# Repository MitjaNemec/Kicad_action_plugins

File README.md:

## NOTICE ##

These plugins work only on old KiCad version (5.1.x).

The plugins that work under newer versions (V5, V6, ...) should be available under the KiCad's built in Plugin and Content Manager (PCM).

Currently (2023) there are four plugins available:
- Replicate Layout plugin (https://github.com/MitjaNemec/ReplicateLayout)
- Place Footprints plugin (https://github.com/MitjaNemec/PlaceFootprints)
- Save/Restore layout plugin (https://github.com/MitjaNemec/SaveRestoreLayout)
- Archive 3D models plugin (https://github.com/MitjaNemec/Archive3DModels)

# KiCad Action Plugins

This repository contains KiCad pcbnew Action Plugins.

__All plugins have been tested on Kicad 5.1.x__ on Windows 7 / Windows 10. You need to have `KICAD_SCRIPTING_WXPYTHON` enabled. They should also work on GNU/Linux distributions and MacOS, even with Python3.

**KiCad V6 info**

Plugins for KiCad V6 will be avialible in KiCads __Plugin and Content Manager__ as they are ported. Some of them will not be ported.

## Installation

The following instructions are for KiCad 5.1.x

### Windows 7/Windows 10

Install the plugins in:
    `%APPDATA%\scripting\plugins` (which most commonly translates to `C:\Users\username\AppData\Roaming\kicad\scripting\plugins`)

### GNU/Linux

Install the plugins in:
    `~/.kicad/scripting/plugins` or
    `~/.kicad_plugins`

If you have no other action plugins, you can use this script:

```
 SPDIR=~/.kicad_plugins
 mkdir -pv `dirname ${SPDIR}` 2>/dev/null
 cd `dirname ${SPDIR}` && git clone --depth 1 git@github.com:MitjaNemec/Kicad_action_plugins.git && \
  ln -s Kicad_action_plugins `basename ${SPDIR}` && cd ${SPDIR} && echo && \
  echo "Installed action plugins:" && find . -d 1 -type d |grep -v '.git' |sed 's/^\.\// * /'
```

To update your action plugins from this repository in future:

```
 SPDIR=~/.kicad_plugins
 cd ${SPDIR} && git pull
```

### Mac

Install the plugins in:
    `~/Library/Application Support/kicad/scripting/plugins` or on newer versions (eg. 5.1.10)
    `~/Library/Preferences/kicad/scripting/plugins`

If you have no other action plugins, you can use this script:

```
 SPDIR=~/Library/Preferences/kicad/scripting/plugins
 mkdir -pv `dirname ${SPDIR}` 2>/dev/null
 cd `dirname ${SPDIR}` && git clone --depth 1 git@github.com:MitjaNemec/Kicad_action_plugins.git && \
  ln -s Kicad_action_plugins `basename ${SPDIR}` && cd ${SPDIR} && echo && \
  echo "Installed action plugins:" && find . -d 1 -type d |grep -v '.git' |sed 's/^\.\// * /'
```

To update your action plugins from this repository in future:

```
 SPDIR=~/Library/Preferences/kicad/scripting/plugins
 cd ${SPDIR} && git pull
```

## Plugins
 
### Replicate layout

The purpose of this plugin is to replicate layout sections. The replication is based upon hierarchical sheets in eeschema.
The basic requirement for replication is that the section to be replicated (source) is completely contained within a single hierarchical sheet, and replicated sections (destination) are just copies of the same sheet. Complex hierarchies are supported therefore replicated sheet can contain subsheets. The plugin replicates footprints, zones, tracks, text adn drawings.

After the section for replication (source section) has been laid out (footprints, tracks, text objects and zones placed) you need to:
1. Place the anchor footprints for the destiantion sections you want to replicate. This defines the position and orientation of replicated sections. You can use [Place footprints] action plugin for this.
2. Select the same anchor footprint within the source section.
3. Run the plugin.
4. Choose which hierarchical level you wish to replicate.
5. Select which sheets you want to replicate (default is all of them)
6. Select whether you want to replicate also tracks, zones and/or text objects.
7. Select whether you want to replicate tracks/zones/text which intersect the pivot bounding box or just those contained within the bounding box.
8. Select whether you want to delete already laid out tracks/zones/text (this is useful when updating an already replicated layout).
9. Hit OK.

By default, only objects which are fully contained in the bounding box constituted by all the footprints in the section will be replicated. You can select to also replicate zones and tracks which intersect this bounding box. Additionally, tracks, text and zones which are already laid out in the replicated bounding boxes can be removed (useful when updating). Note that bounding boxes are squares aligned with the x and y axis, regardless of section orientation.

Example replication of a complex hierarchical project. Replicating inner sheet first, then outer.

### Place footprints

This plugin will place footprints in:
- in line
- circular
- in square matrix

The plugins for placement are selected either by consecutive reference numbers or by same ID on different hierarchical sheets.

If you want to place the footprints by consecutive reference numbers you have to
1. select a footprint which is first in the sequence to be placed
2. run the plugin
3. select which place by reference number
4. choose which footprint in the sequence you want to place
5. select the arrangement (linear, matrix, circular)
6. select place dimension (step in x and y axes in linear and matrix mode and angle step and radius in circular mode)
7. run the plugin

If you want to place the footprints by same ID with
1. select a footprint which is first in the sequence to be placed
2. run the plugin
3. select the hierarchical level by which the footprints will be placed (in complex hierarchies)
4. choose from which sheets you want the footprint to place
5. select the arrangement (linear, matrix, circular)
6. select place dimension (step in x and y axes in linear and matrixc mode and angle step and radius in circlar mode)
7. run the plugin

Example of place by reference number

Example of place by sheet ID

### Delete Selected

This plugin deletes selected items. Items can be: zones and/or tracks and/or footprints. The main intention is to delete selected tracks in order to redo parts of the layout.

To run the plugin:
1. Select items you want to delete (note that in KiCad it is different if you start your selection box from left or right)
2. Run the plugin
3. Select what you want to delete
4. Hit OK

### pad2pad track distance

This plugin calculates the shortest distance between two pads. Use with caution because the result is not always correct as the algorithm follows the track layout. Also, the Via distance is not accounted for. The following picture shows an example where the distance is not correct. Here, the algorithm calculates the distance from the first pad to pin #4 and then to the other pad. It does not consider the connection between the two tracks at the encircled area where they actually branch off making the measured distance longer than it actually is.

For complex tracks (GND, Supply rails) the calculation can take quite some time.

To run the plugin:
1. Select two pads to measure the distance between
2. Run the plugin
3. Select what you want to delete
4. Hit OK

### net2net min distance

This plugin calculates the shortest distance between two tracks on different nets. To use, select one pad on first net and one pad on second net and run the plugin.

### Archive project

This plugin archives the project thus making it portable.

The schematics archive is achieved via the project cache library. The project cache library is copied to project-archive.lib which is modified and added to the project symbol library table (if the table does not exist it is created). Also the links to the symbols within the schematics are modified so that they point to the symbols within the archive library. Afterwards, the cache library is deleted. Eeschema will recreate a correct cache library the next time the schematics are edited.

The archiving of the pcb and its footprints is already implemented within pcbnew.

The 3D models archive is placed in "shapes3D" subfolder where all 3D models are copied.
Then, the links to the models within the layout (.kicad_pcb) file are modified so that they point to the archived 3D models with a path relative to the project folder.

The plugin is run from pcbnew. When the plugin is run, eeschema has to be closed. If the plugin finished successfully, it automatically closes pcbnew. This behaviour is expected and required to perform the operation.

If the project is modified later it should be archived again in order to stay portable. If a symbol of a unit has to be replaced, all units with the same symbol have to be deleted.

### Swap pins

This plugin swaps two pads (in layout) and their corresponding pins (in schematics). The pins in the schematics have to be connected to a local or global label or hierarchical label either directly or through a short wire segment. The plugin also works across multi-unit parts and/or across different hierarchical levels.

Only one pin can be connected. Currently "no connection" flags are not supported. Eeschema has to be closed when the plugin is executed in pcbnew. Once the plugin is done, you should save the layout. Note that using undo will only undo the change in the layout, but not the change in the schematics. To reverse the operation, you can run the plugin again.

Example of pin swapping

### Swap units

This plugin swaps two units (in layout) and r units (in schematics). Eeschema has to be closed when the plugin is executed in pcbnew. Unit swapping work across hierarchical pages.  Note that using undo will only undo the change in the layout, but not the change in the schematics. To reverse the operation, you can run the plugin again.

Example of unit swapping

### Length stats

This plugin displays length of all tracks on selected nets. This can be used for length matching.

Workflow:
1. Select tracks or pads on nets you want the length displayed. You can also select a footprint(s)
2. Run the plugin. You can remove redundant nets
3. Lay the tracks
4. Close the track length window

Example:

### Save/Restore Layout

This plugin saves the partial layout of a selected pcb (only specific hierarchical level is saved). This layout can be imported into another pcb, if it is based upon the same hierarchical subsheets. The equality is tested and checked.

Workflow:
1. Select one footprint which is in the hierarchy that you want to save the layout for.
2. Run the plugin and choose "Save layout"
3. Select into which file should the layout be saved
4. Create a new project. Copy the chosen .sch files used for hierarchy to the project folder and link it into schematics
5. Create a new layout.
6. Place and select the anchor footprint. This defines the position and orientation of restored layout.
7. Run the plugin.
8. Choose "Restore layout"
9: Select in which file is tha layout data stored
10. Voila, observe restored layout

Example:

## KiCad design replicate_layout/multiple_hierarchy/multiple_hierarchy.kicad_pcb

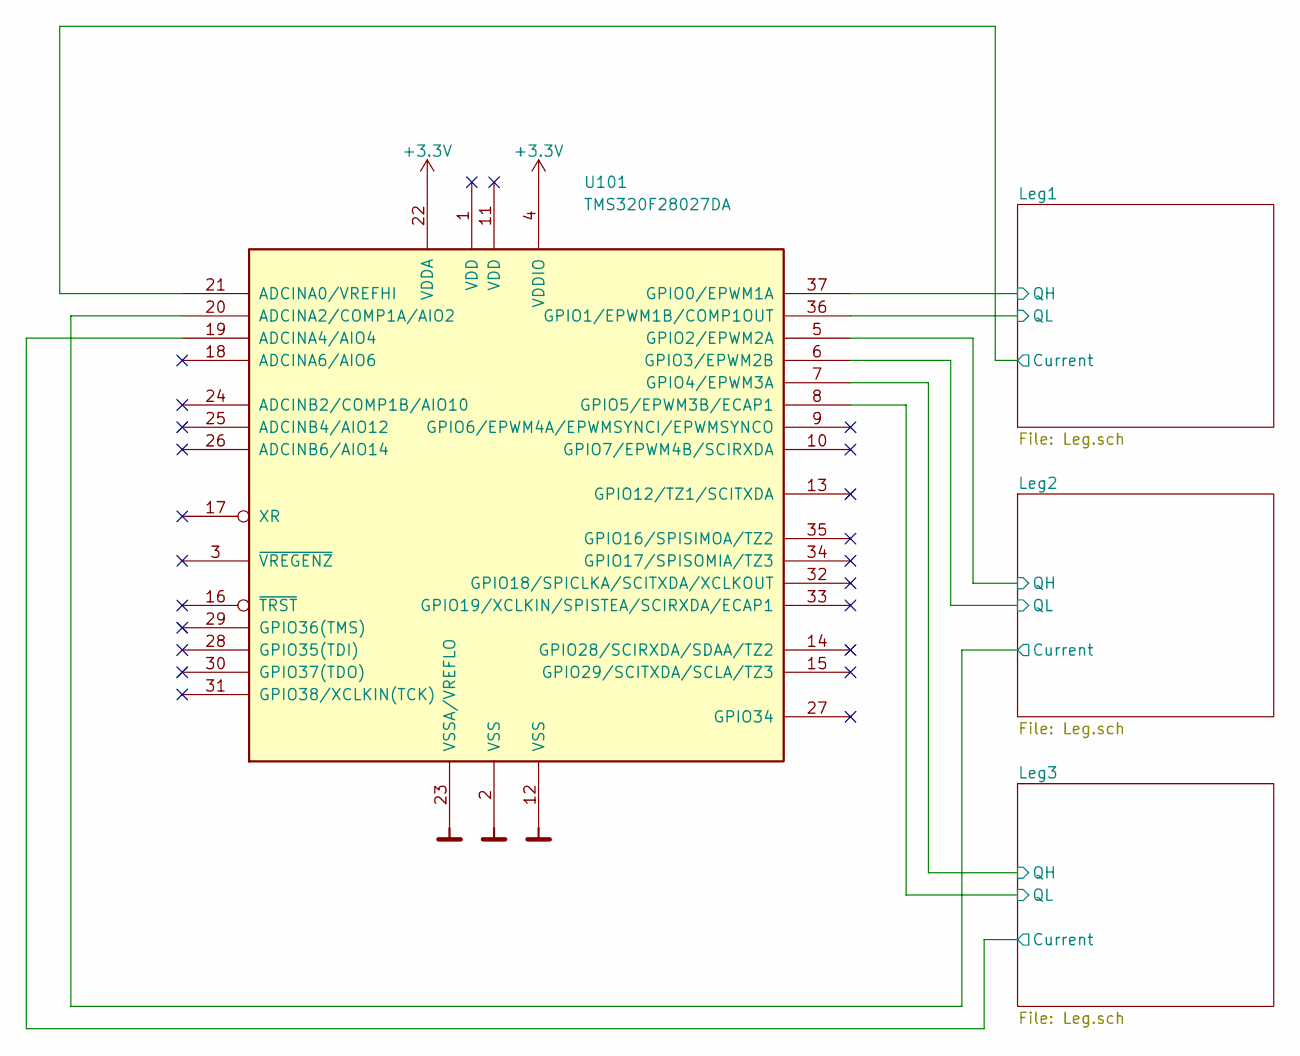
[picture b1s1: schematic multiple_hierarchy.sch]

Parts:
U101: TMS320F28027DA; TSSOP-38_4.4x9.7mm_P0.5mm

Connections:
+3V3: U101.4 (VDDIO), U101.22 (VDDA); also elsewhere on the board
-VDC: U101.2 (VSS), U101.12 (VSS), U101.23 (VSSA/VREFLO); also elsewhere on the board
/Leg1/Current: U101.21 (ADCINA0/VREFHI); also elsewhere on the board
/Leg1/QH: U101.37 (GPIO0/EPWM1A); also elsewhere on the board
/Leg1/QL: U101.36 (GPIO1/EPWM1B/COMP1OUT); also elsewhere on the board
/Leg2/Current: U101.20 (ADCINA2/COMP1A/AIO2); also elsewhere on the board
/Leg2/QH: U101.5 (GPIO2/EPWM2A); also elsewhere on the board
/Leg2/QL: U101.6 (GPIO3/EPWM2B); also elsewhere on the board
/Leg3/Current: U101.19 (ADCINA4/AIO4); also elsewhere on the board
/Leg3/QH: U101.7 (GPIO4/EPWM3A); also elsewhere on the board
/Leg3/QL: U101.8 (GPIO5/EPWM3B/ECAP1); also elsewhere on the board
/Power_extra/QH: U101.9 (GPIO6/EPWM4A/EPWMSYNCI/EPWMSYNCO); also elsewhere on the board
/Power_extra/Ql: U101.10 (GPIO7/EPWM4B/SCIRXDA); also elsewhere on the board

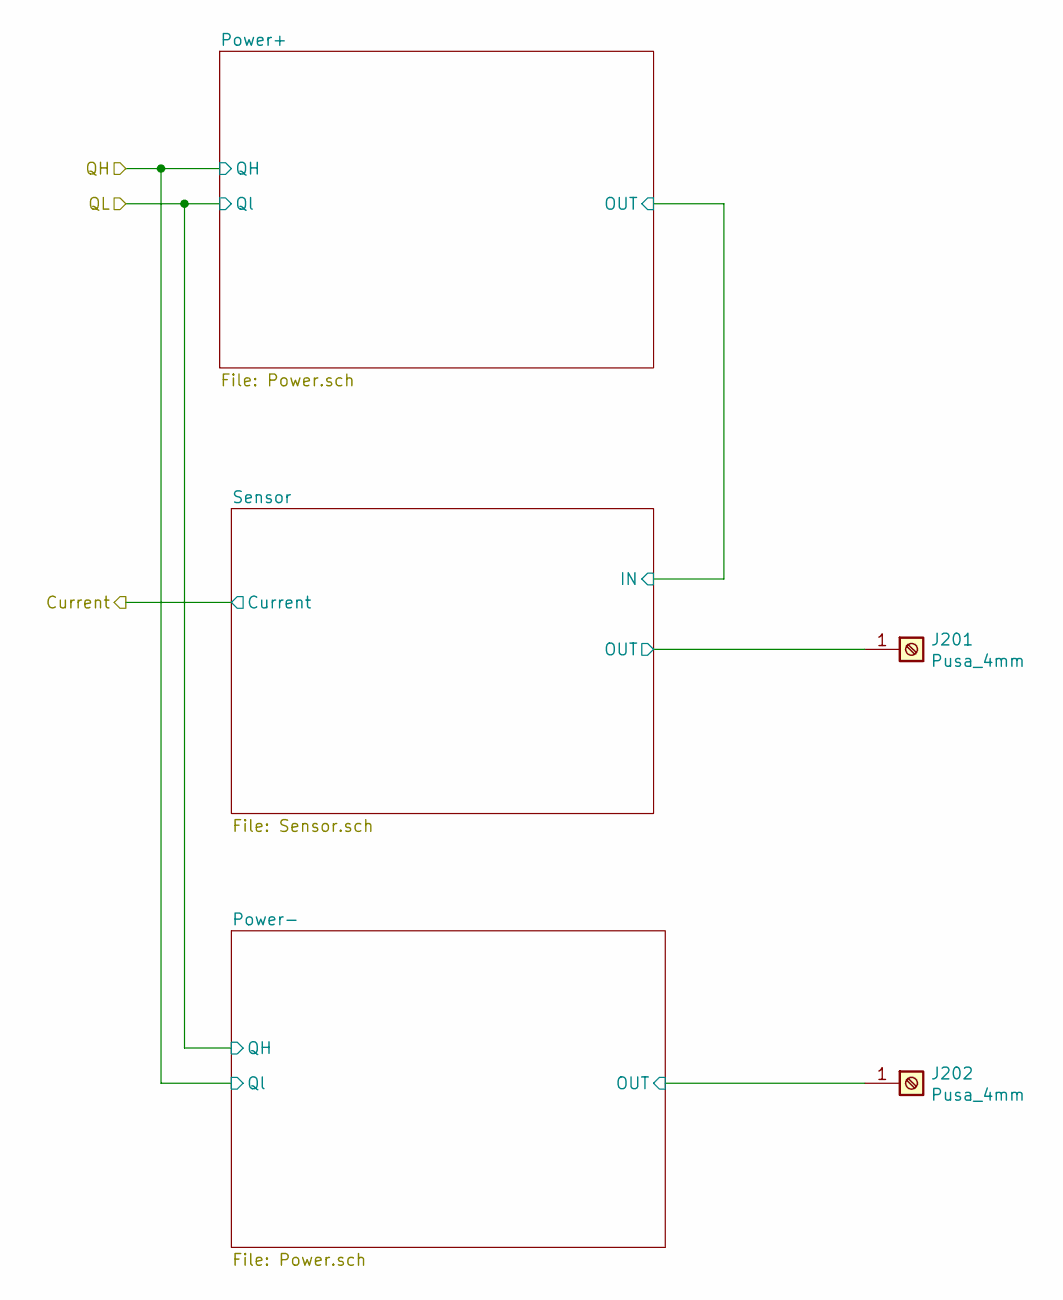
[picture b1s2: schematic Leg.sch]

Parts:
J201, J202: Pusa_4mm

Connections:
/Leg1/Power-/OUT: J202.1; also elsewhere on the board
/Leg1/Sensor/OUT: J201.1; also elsewhere on the board

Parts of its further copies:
J601, J602, J1001, J1002: Pusa_4mm

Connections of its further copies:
/Leg2/Power-/OUT: J602.1; also elsewhere on the board
/Leg2/Sensor/OUT: J601.1; also elsewhere on the board
/Leg3/Power-/OUT: J1002.1; also elsewhere on the board
/Leg3/Sensor/OUT: J1001.1; also elsewhere on the board

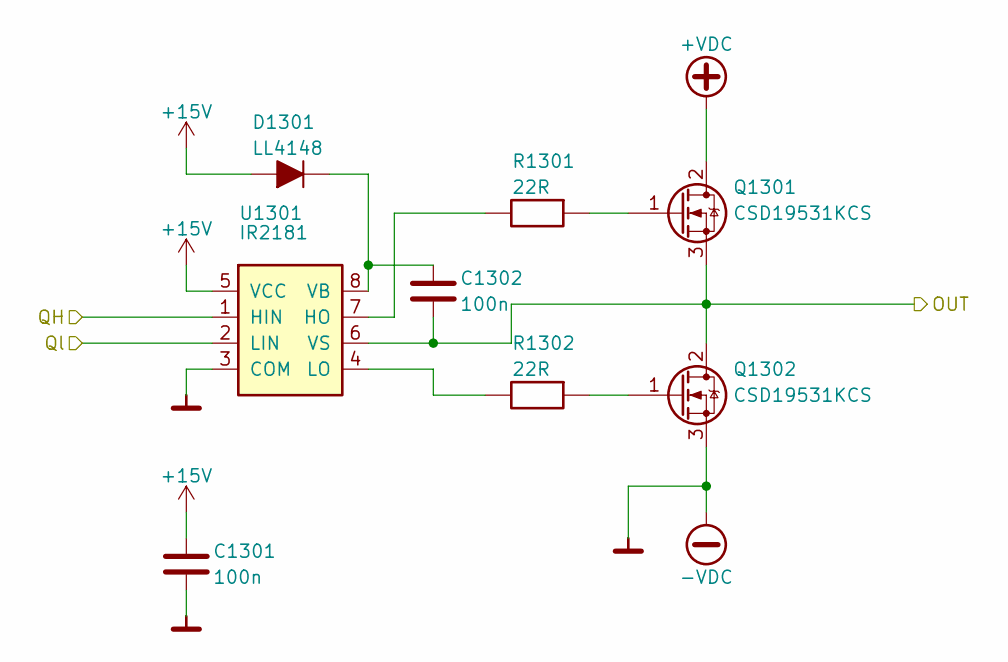
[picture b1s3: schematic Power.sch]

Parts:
C301, C302: 100n; C1206M
D301: LL4148; D_MiniMELF
Q301, Q302: CSD19531KCS; TO-220
R301, R302: 22R; R1206M
U301: IR2181; SO8

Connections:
+15V: C301.1, D301.2 (A), U301.5 (VCC); also elsewhere on the board
+VDC: Q301.2 (D); also elsewhere on the board
-VDC: C301.2, Q302.3 (S), U301.3 (COM); also elsewhere on the board
/Leg1/QH: U301.1 (HIN); also elsewhere on the board
/Leg1/QL: U301.2 (LIN); also elsewhere on the board
/Leg1/Sensor/IN: C302.2, Q301.3 (S), Q302.2 (D), U301.6 (VS); also elsewhere on the board
unnamed: C302.1, D301.1 (K), U301.8 (VB)
unnamed: Q301.1 (G), R301.2
unnamed: Q302.1 (G), R302.2
unnamed: R301.1, U301.7 (HO)
unnamed: R302.1, U301.4 (LO)

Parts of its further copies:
C501, C502, C701, C702, C901, C902, C1101, C1102, C1301, C1302: 100n; C1206M
D501, D701, D901, D1101, D1301: LL4148; D_MiniMELF
Q501, Q502, Q701, Q702, Q901, Q902, Q1101, Q1102, Q1301, Q1302: CSD19531KCS; TO-220
R501, R502, R701, R702, R901, R902, R1101, R1102, R1301, R1302: 22R; R1206M
U501, U701, U901, U1101, U1301: IR2181; SO8

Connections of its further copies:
+15V: C501.1, C701.1, C901.1, C1101.1, C1301.1, D501.2 (A), D701.2 (A), D901.2 (A), D1101.2 (A), D1301.2 (A), U501.5 (VCC), U701.5 (VCC), U901.5 (VCC), U1101.5 (VCC), U1301.5 (VCC); also elsewhere on the board
+VDC: Q501.2 (D), Q701.2 (D), Q901.2 (D), Q1101.2 (D), Q1301.2 (D); also elsewhere on the board
-VDC: C501.2, C701.2, C901.2, C1101.2, C1301.2, Q502.3 (S), Q702.3 (S), Q902.3 (S), Q1102.3 (S), Q1302.3 (S), U501.3 (COM), U701.3 (COM), U901.3 (COM), U1101.3 (COM), U1301.3 (COM); also elsewhere on the board
/Leg1/Power-/OUT: C502.2, Q501.3 (S), Q502.2 (D), U501.6 (VS); also elsewhere on the board
/Leg1/QH: U501.2 (LIN); also elsewhere on the board
/Leg1/QL: U501.1 (HIN); also elsewhere on the board
/Leg2/Power-/OUT: C902.2, Q901.3 (S), Q902.2 (D), U901.6 (VS); also elsewhere on the board
/Leg2/QH: U701.1 (HIN), U901.2 (LIN); also elsewhere on the board
/Leg2/QL: U701.2 (LIN), U901.1 (HIN); also elsewhere on the board
/Leg2/Sensor/IN: C702.2, Q701.3 (S), Q702.2 (D), U701.6 (VS); also elsewhere on the board
/Leg3/Power-/OUT: C1302.2, Q1301.3 (S), Q1302.2 (D), U1301.6 (VS); also elsewhere on the board
/Leg3/QH: U1101.1 (HIN), U1301.2 (LIN); also elsewhere on the board
/Leg3/QL: U1101.2 (LIN), U1301.1 (HIN); also elsewhere on the board
/Leg3/Sensor/IN: C1102.2, Q1101.3 (S), Q1102.2 (D), U1101.6 (VS); also elsewhere on the board
unnamed: C502.1, D501.1 (K), U501.8 (VB)
unnamed: C702.1, D701.1 (K), U701.8 (VB)
unnamed: C902.1, D901.1 (K), U901.8 (VB)
unnamed: C1102.1, D1101.1 (K), U1101.8 (VB)
unnamed: C1302.1, D1301.1 (K), U1301.8 (VB)
unnamed: Q501.1 (G), R501.2
unnamed: Q502.1 (G), R502.2
unnamed: Q701.1 (G), R701.2
unnamed: Q702.1 (G), R702.2
unnamed: Q901.1 (G), R901.2
unnamed: Q902.1 (G), R902.2
unnamed: Q1101.1 (G), R1101.2
unnamed: Q1102.1 (G), R1102.2
unnamed: Q1301.1 (G), R1301.2
unnamed: Q1302.1 (G), R1302.2
unnamed: R501.1, U501.7 (HO)
unnamed: R502.1, U501.4 (LO)
unnamed: R701.1, U701.7 (HO)
unnamed: R702.1, U701.4 (LO)
unnamed: R901.1, U901.7 (HO)
unnamed: R902.1, U901.4 (LO)
unnamed: R1101.1, U1101.7 (HO)
unnamed: R1102.1, U1101.4 (LO)
unnamed: R1301.1, U1301.7 (HO)
unnamed: R1302.1, U1301.4 (LO)

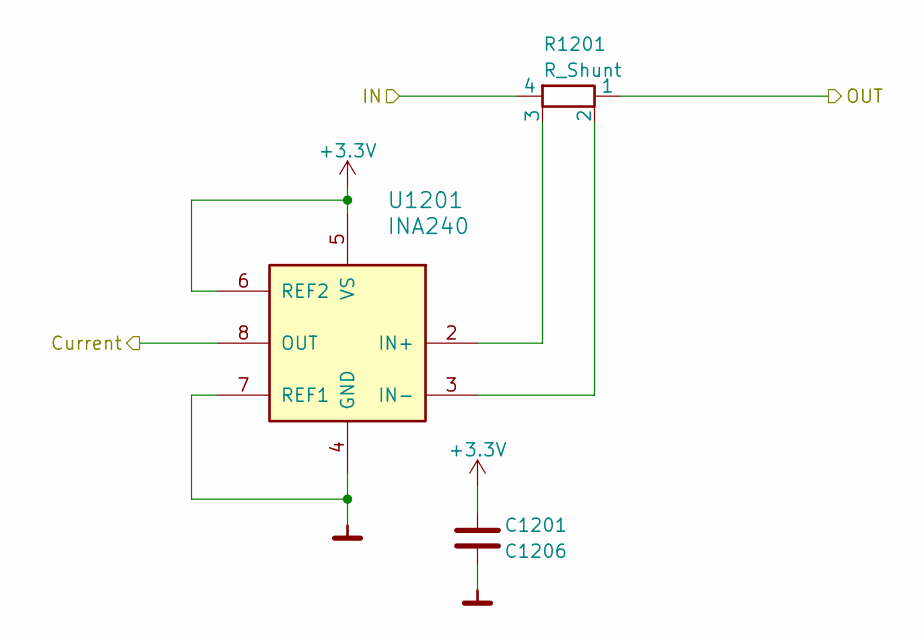
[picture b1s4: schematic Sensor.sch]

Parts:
C401: C1206; C1206M
R401: R_Shunt; RM
U401: INA240; TSSOP-8_4.4x3mm_P0.65mm

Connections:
+3V3: C401.1, U401.5 (VS), U401.6 (REF2); also elsewhere on the board
-VDC: C401.2, U401.4 (GND), U401.7 (REF1); also elsewhere on the board
/Leg1/Current: U401.8 (OUT); also elsewhere on the board
/Leg1/Sensor/IN: R401.4; also elsewhere on the board
/Leg1/Sensor/OUT: R401.1; also elsewhere on the board
unnamed: R401.2, U401.3 (IN-)
unnamed: R401.3, U401.2 (IN+)

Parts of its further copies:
C801, C1201: C1206; C1206M
R801, R1201: R_Shunt; RM
U801, U1201: INA240; TSSOP-8_4.4x3mm_P0.65mm

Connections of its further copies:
+3V3: C801.1, C1201.1, U801.5 (VS), U801.6 (REF2), U1201.5 (VS), U1201.6 (REF2); also elsewhere on the board
-VDC: C801.2, C1201.2, U801.4 (GND), U801.7 (REF1), U1201.4 (GND), U1201.7 (REF1); also elsewhere on the board
/Leg2/Current: U801.8 (OUT); also elsewhere on the board
/Leg2/Sensor/IN: R801.4; also elsewhere on the board
/Leg2/Sensor/OUT: R801.1; also elsewhere on the board
/Leg3/Current: U1201.8 (OUT); also elsewhere on the board
/Leg3/Sensor/IN: R1201.4; also elsewhere on the board
/Leg3/Sensor/OUT: R1201.1; also elsewhere on the board
unnamed: R801.2, U801.3 (IN-)
unnamed: R801.3, U801.2 (IN+)
unnamed: R1201.2, U1201.3 (IN-)
unnamed: R1201.3, U1201.2 (IN+)

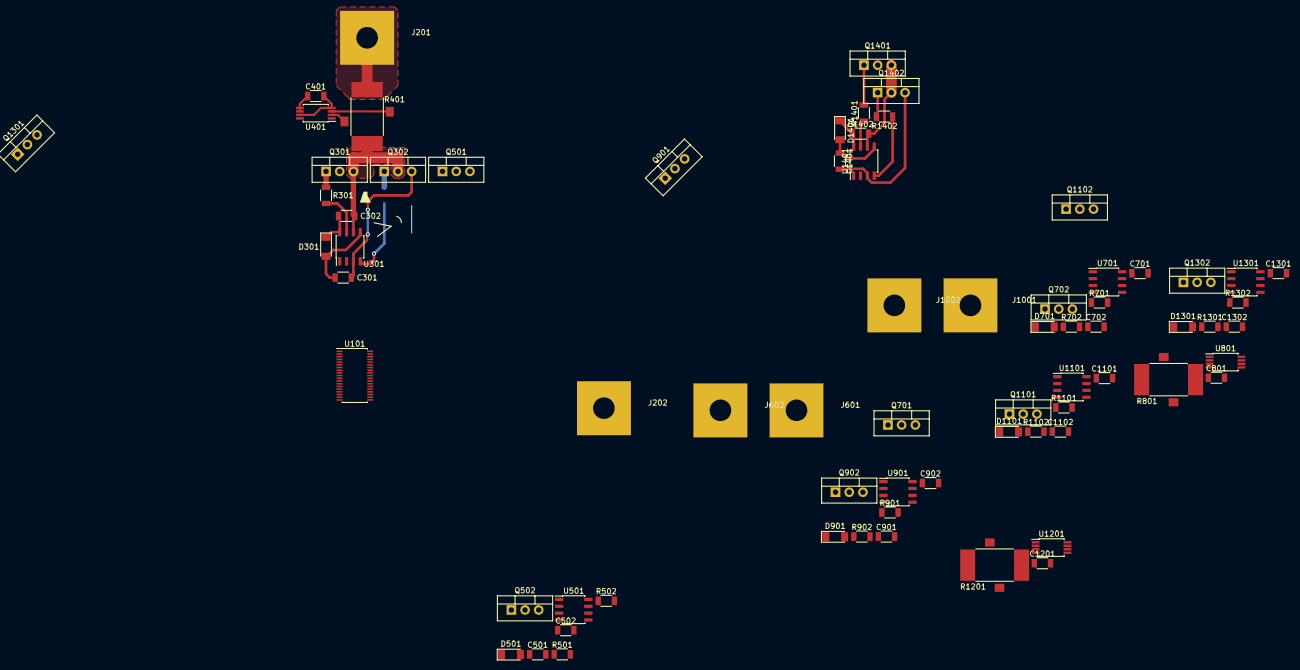
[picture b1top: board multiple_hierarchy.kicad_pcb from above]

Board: 2 copper layers, 72 parts (1 on the bottom side), 66 nets.

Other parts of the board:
C1401, C1402: 100n; C1206M
D1401: LL4148; D_MiniMELF
Q1401, Q1402: CSD19531KCS; TO-220
R1401, R1402: 22R; R1206M
U1401: IR2181; SO8

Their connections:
+15V: C1401.1, D1401.2, U1401.5; also elsewhere on the board
+VDC: Q1401.2; also elsewhere on the board
-VDC: C1401.2, Q1402.3, U1401.3; also elsewhere on the board
/Power_extra/OUT: C1402.2, Q1401.3, Q1402.2, U1401.6
/Power_extra/QH: U1401.1; also elsewhere on the board
/Power_extra/Ql: U1401.2; also elsewhere on the board
unnamed: C1402.1, D1401.1, U1401.8
unnamed: Q1401.1, R1401.2
unnamed: Q1402.1, R1402.2
unnamed: R1401.1, U1401.7
unnamed: R1402.1, U1401.4

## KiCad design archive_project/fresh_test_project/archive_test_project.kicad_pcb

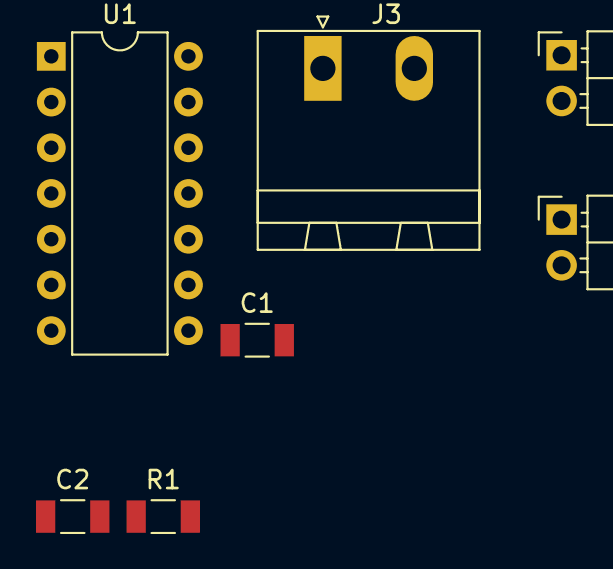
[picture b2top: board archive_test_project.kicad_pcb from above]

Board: 2 copper layers, 7 parts (0 on the bottom side), 5 nets, no tracks yet.

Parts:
C1, C2: C; C_1206_3216Metric
J1, J2: Conn_01x02; PinHeader_1x02_P2.54mm_Horizontal
J3: Screw_Terminal_01x02; PhoenixContact_MSTBA_2,5_2-G-5,08_1x02_P5.08mm_Horizontal
R1: R; R_1206_3216Metric
U1: LM318J; DIP-14_W7.62mm

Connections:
+15V: C1.1, J2.2, U1.11
/subsheet/IN: R1.2, U1.4, U1.10
/subsheet/OUT: C2.1, J3.1, R1.1
GND: C1.2, C2.2, J1.1, J2.1, J3.2, U1.6
unnamed: J1.2, U1.5

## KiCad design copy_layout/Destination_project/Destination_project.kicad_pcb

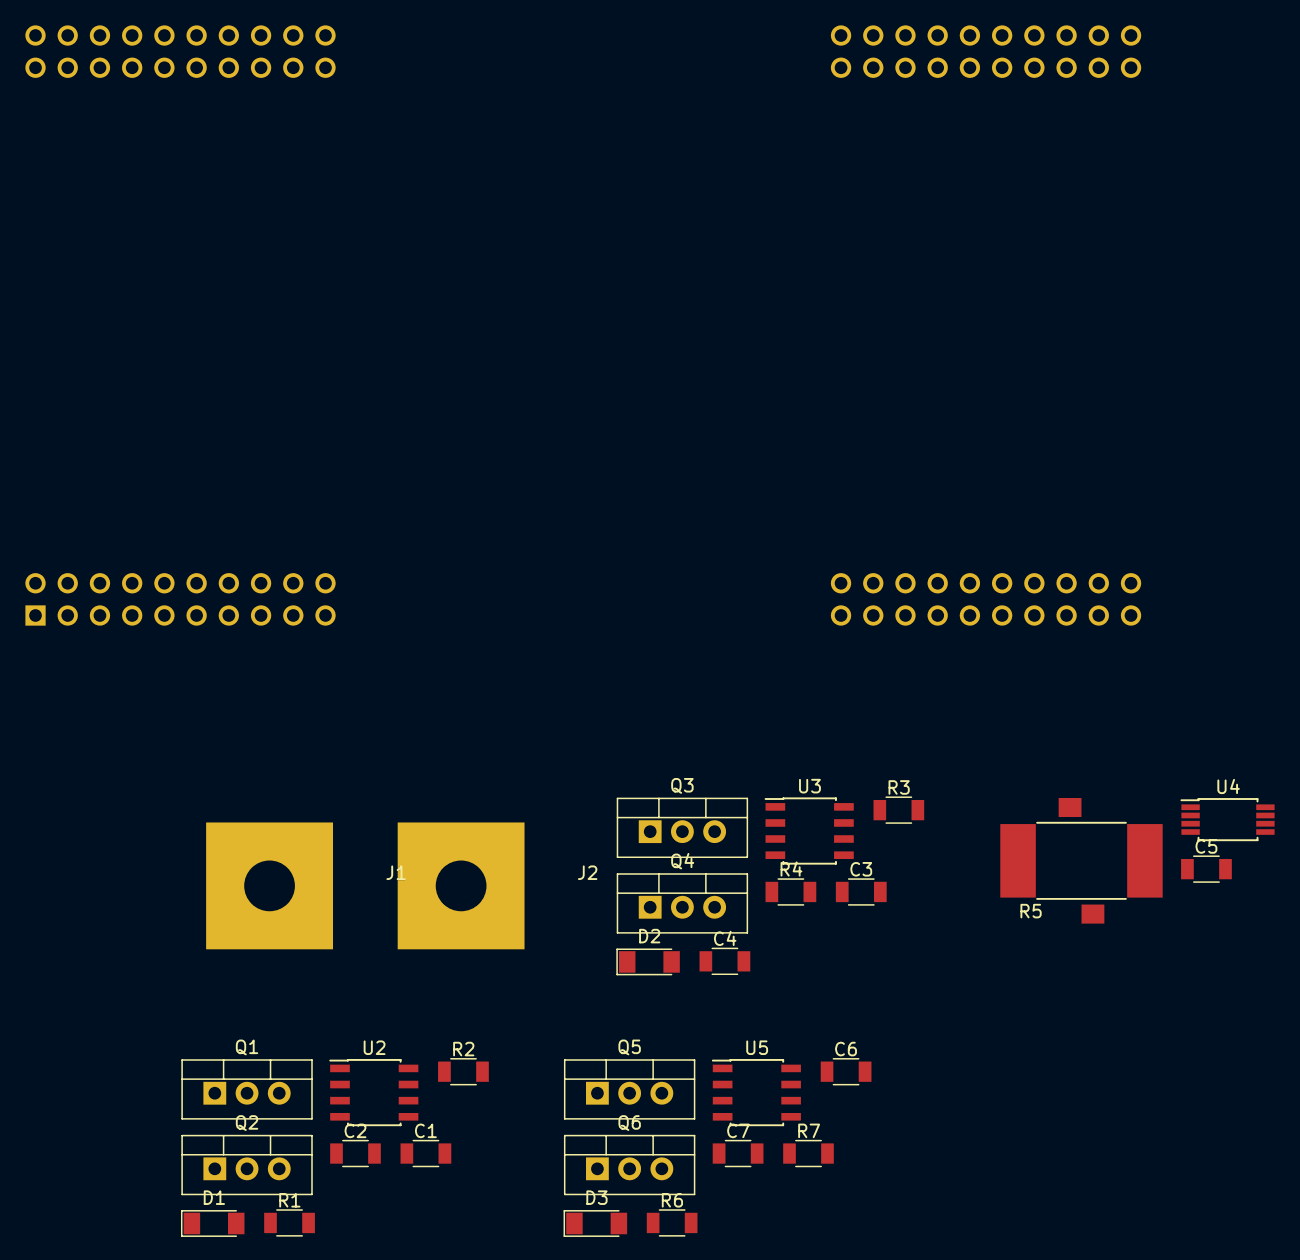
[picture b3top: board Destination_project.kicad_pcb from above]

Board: 2 copper layers, 30 parts (0 on the bottom side), 31 nets, no tracks yet.

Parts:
C1, C2, C3, C4, C6, C7: 100n; C1206M
C5: C1206; C1206M
D1, D2, D3: LL4148; D_MiniMELF
J1, J2: Pusa_4mm
Q1, Q2, Q3, Q4, Q5, Q6: CSD19531KCS; TO-220
R1, R2, R3, R4, R6, R7: 22R; R1206M
R5: R_Shunt; RM
U1: LAUNCHXL-F28379D; 28379D_launchpad
U2, U3, U5: IR2181; SO8
U4: INA240; TSSOP-8_4.4x3mm_P0.65mm

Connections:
+3V3: C5.1, U1.1, U1.41, U4.5, U4.6
+5V: U1.21, U1.61
+15V: C1.1, C3.1, C6.1, D1.2, D2.2, D3.2, U2.5, U3.5, U5.5
+VDC: Q1.2, Q3.2, Q5.2
-VDC: C1.2, C3.2, C5.2, C6.2, Q2.3, Q4.3, Q6.3, U1.20, U1.22, U1.60, U1.62, U2.3, U3.3, U4.4, U4.7, U5.3
/Leg/Current: U1.24, U4.8
/Leg/Power-/OUT: C7.2, J2.1, Q5.3, Q6.2, U5.6
/Leg/QH: U1.40, U3.1, U5.2
/Leg/QL: U1.39, U3.2, U5.1
/Leg/Sensor/IN: C4.2, Q3.3, Q4.2, R5.4, U3.6
/Leg/Sensor/OUT: J1.1, R5.1
/power/OUT: C2.2, Q1.3, Q2.2, U2.6
/power/QH: U1.38, U2.1
/power/Ql: U1.37, U2.2
unnamed: C2.1, D1.1, U2.8
unnamed: C4.1, D2.1, U3.8
unnamed: C7.1, D3.1, U5.8
unnamed: Q1.1, R1.2
unnamed: Q2.1, R2.2
unnamed: Q3.1, R3.2
unnamed: Q4.1, R4.2
unnamed: Q5.1, R6.2
unnamed: Q6.1, R7.2
unnamed: R1.1, U2.7
unnamed: R2.1, U2.4
unnamed: R3.1, U3.7
unnamed: R4.1, U3.4
unnamed: R5.2, U4.3
unnamed: R5.3, U4.2
unnamed: R6.1, U5.7
unnamed: R7.1, U5.4

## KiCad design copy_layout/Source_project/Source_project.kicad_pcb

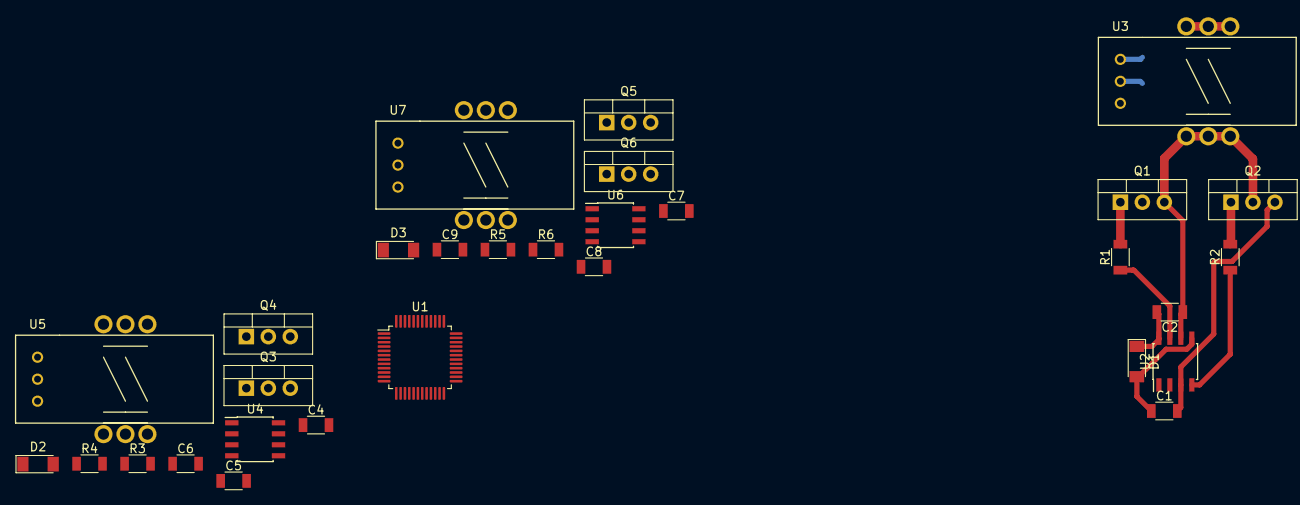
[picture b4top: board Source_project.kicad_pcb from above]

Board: 2 copper layers, 31 parts (1 on the bottom side), 34 nets.

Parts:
C1, C2, C3, C4, C5, C6, C7, C8, C9: 100n; C1206M
D1, D2, D3: LL4148; D_MiniMELF
Q1, Q2, Q3, Q4, Q5, Q6: CSD19531KCS; TO-220
R1, R2, R3, R4, R5, R6: 22R; R1206M
U1: TMS320F28027PT; LQFP-48_7x7mm_P0.5mm
U2, U4, U6: IR2181; SO8
U3, U5, U7: LTS_15

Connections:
+1V8: U1.32, U1.43
+3V3: C3.2, C6.2, C9.2, U1.11, U1.35, U3.+, U5.+, U7.+
+12V: C1.1, C4.1, C7.1, D1.2, D2.2, D3.2, Q1.2, Q3.2, Q5.2, U2.5, U4.5, U6.5
/Leg1/HIN: U1.29, U2.1
/Leg1/LIN: U1.28, U2.2
/Leg1/TOK: U1.10, U3.OUT
/Leg2/HIN: U1.37, U4.1
/Leg2/LIN: U1.38, U4.2
/Leg2/TOK: U1.8, U5.OUT
/Leg3/HIN: U1.39, U6.1
/Leg3/LIN: U1.40, U6.2
/Leg3/TOK: U1.9, U7.OUT
GND: C1.2, C3.1, C4.2, C6.1, C7.2, C9.1, Q2.3, Q4.3, Q6.3, U1.12, U1.33, U1.44, U2.3, U3.0, U4.3, U5.0, U6.3, U7.0
unnamed: C2.1, Q1.3, Q2.2, U2.6, U3.1, U3.2, U3.3
unnamed: C2.2, D1.1, U2.8
unnamed: C5.1, R4.1, U4.4
unnamed: C5.2, D2.1, U4.8
unnamed: C8.1, R6.1, U6.4
unnamed: C8.2, D3.1, U6.8
unnamed: Q1.1, R1.2
unnamed: Q2.1, R2.2
unnamed: Q3.1, R3.2
unnamed: Q3.3, Q4.2, U5.1, U5.2, U5.3
unnamed: Q4.1, R4.2
unnamed: Q5.1, R5.2
unnamed: Q5.3, Q6.2, U7.1, U7.2, U7.3
unnamed: Q6.1, R6.2
unnamed: R1.1, U2.7
unnamed: R2.1, U2.4
unnamed: R3.1, U4.7
unnamed: R5.1, U6.7
unnamed: U3.4, U3.5, U3.6
unnamed: U5.4, U5.5, U5.6
unnamed: U7.4, U7.5, U7.6

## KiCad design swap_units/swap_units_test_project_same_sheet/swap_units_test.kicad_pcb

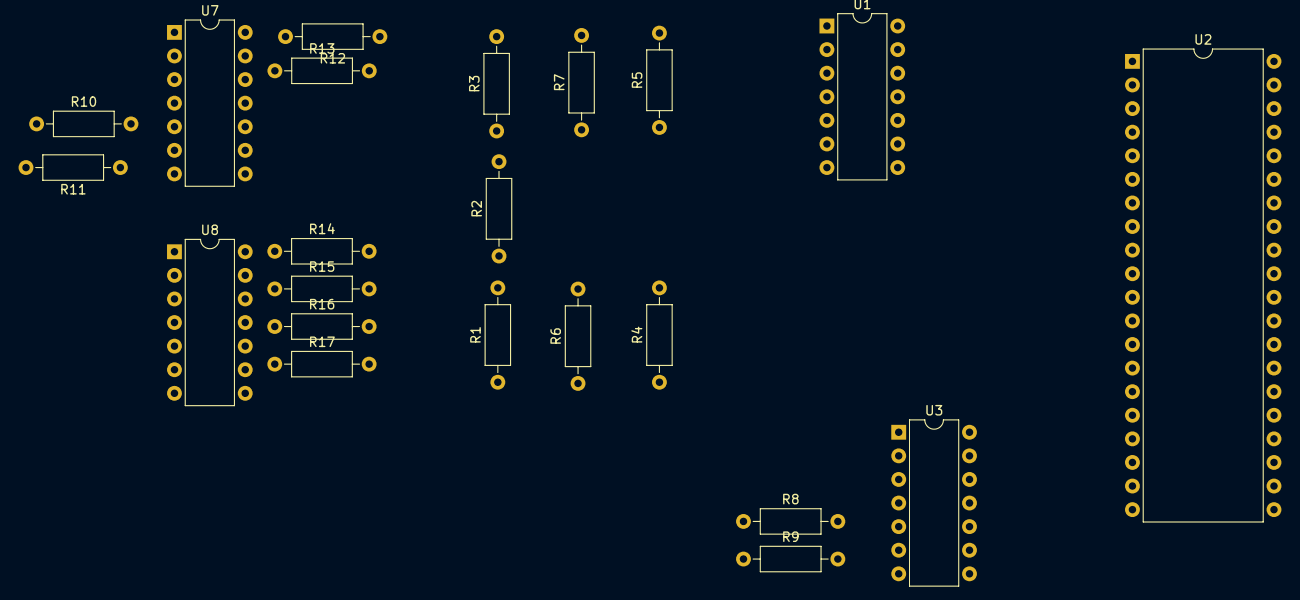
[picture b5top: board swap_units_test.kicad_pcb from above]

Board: 2 copper layers, 22 parts (0 on the bottom side), 20 nets, no tracks yet.

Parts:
R1, R2, R3, R4, R5, R6, R7, R8, R9, R10, R11, R12, R13, R14, R15, R16, R17: R; R_Axial_DIN0207_L6.3mm_D2.5mm_P10.16mm_Horizontal
U1, U3, U7, U8: LM324; DIP-14_W7.62mm
U2: PIC18F452-IP; DIP-40_W15.24mm

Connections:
+5V: R1.1, R4.1, R6.1, R8.1, R10.1, R12.1, R14.1, R16.1, U1.4, U2.11, U2.32
/Level1/Level2b/out_level_2: U3.13, U3.14
/Level1/Level3a/out_level_1: U7.13, U7.14
/Level1/Level3a/out_level_2: U7.6, U7.7
/Level1/Level3b/out_level_1: U8.13, U8.14
/Level1/Level3b/out_level_2: U8.6, U8.7
/Level1/out_level_1: U1.8, U1.9, U2.2
/Level1/out_level_2: U1.13, U1.14, U2.3
GND: R3.2, R5.2, R7.2, R9.2, R11.2, R13.2, R15.2, R17.2, U1.11, U2.12, U2.31
unnamed: R1.2, R2.1, U1.5
unnamed: R2.2, R3.1, U1.3
unnamed: R4.2, R5.1, U1.10
unnamed: R6.2, R7.1, U1.12
unnamed: R8.2, R9.1, U3.12
unnamed: R10.2, R11.1, U7.5
unnamed: R12.2, R13.1, U7.12
unnamed: R14.2, R15.1, U8.5
unnamed: R16.2, R17.1, U8.12
unnamed: U1.6, U1.7, U2.4
unnamed: U1.1, U1.2, U2.5

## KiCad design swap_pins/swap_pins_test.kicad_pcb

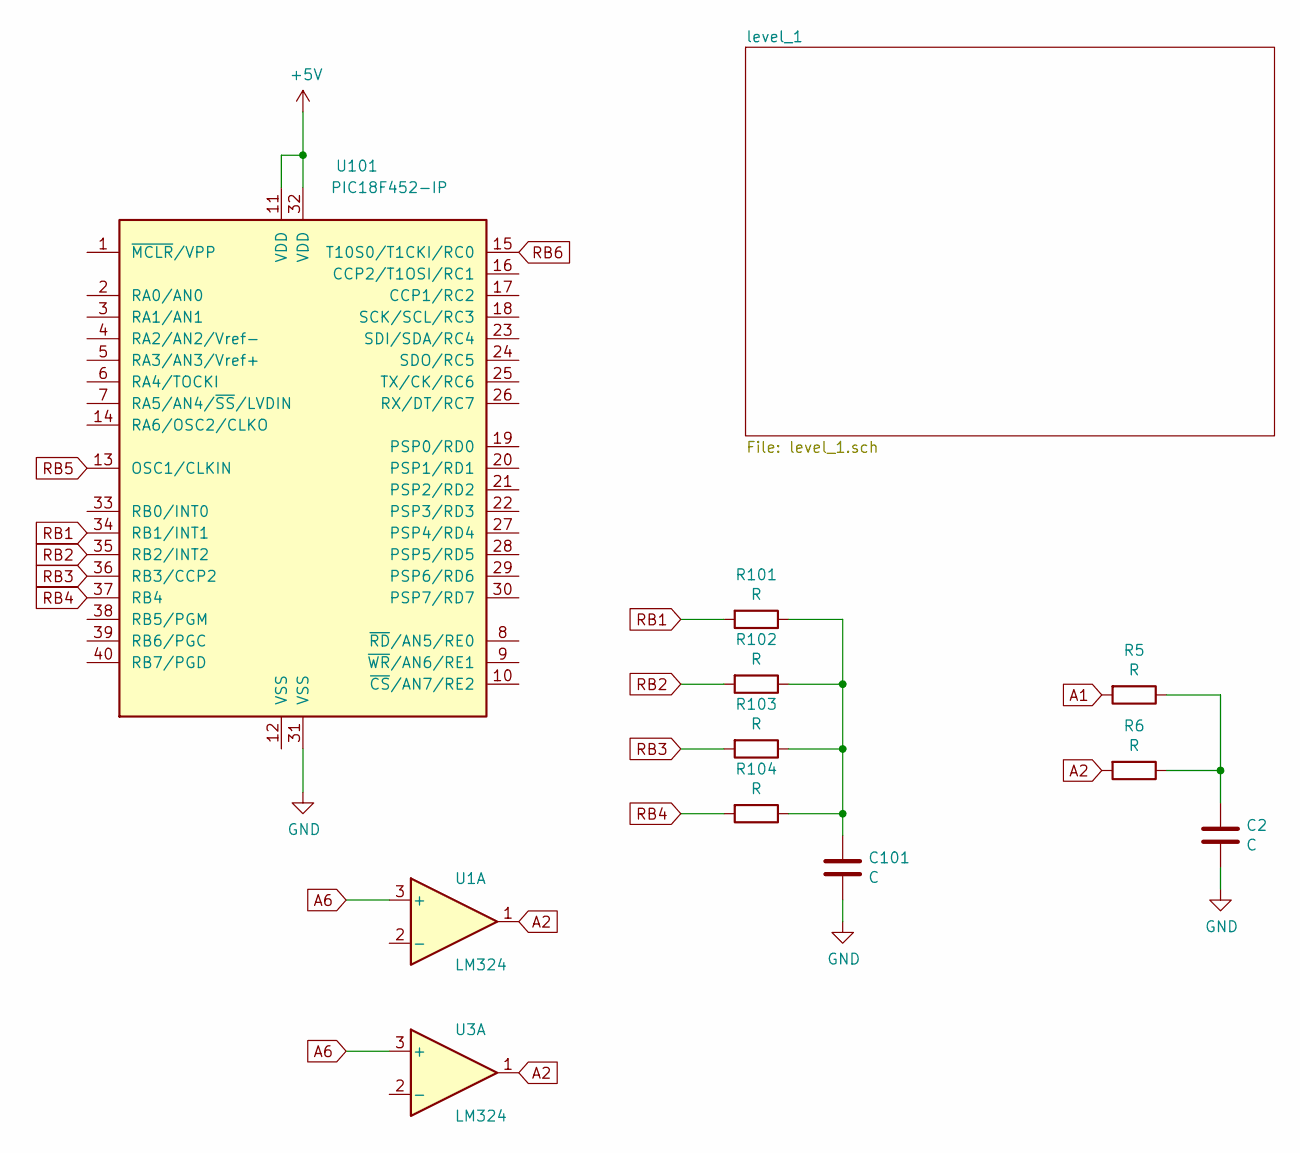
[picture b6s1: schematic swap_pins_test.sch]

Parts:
C2, C101: C; C_Disc_D7.5mm_W5.0mm_P5.00mm
R5, R6, R101, R102, R103, R104: R; R_Axial_DIN0614_L14.3mm_D5.7mm_P20.32mm_Horizontal
U1, U3: LM324; DIP-14_W7.62mm
U101: PIC18F452-IP; DIP-40_W15.24mm

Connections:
+5V: U101.11 (VDD), U101.32 (VDD); also elsewhere on the board
A1: R5.2; also elsewhere on the board
A2: R6.2, U1.1, U3.1
A6: U1.3 (+), U3.3 (+)
GND: C2.2, C101.2, U101.31 (VSS); also elsewhere on the board
unnamed: C2.1, R5.1, R6.1
unnamed: C101.1, R101.1, R102.1, R103.1, R104.1
RB1: R101.2, U101.34 (RB1/INT1)
RB2: R102.2, U101.35 (RB2/INT2)
RB3: R103.2, U101.36 (RB3/CCP2)
RB4: R104.2, U101.37 (RB4)
RB5: U101.13 (OSC1/CLKIN)
RB6: U101.15 (T10S0/T1CKI/RC0)

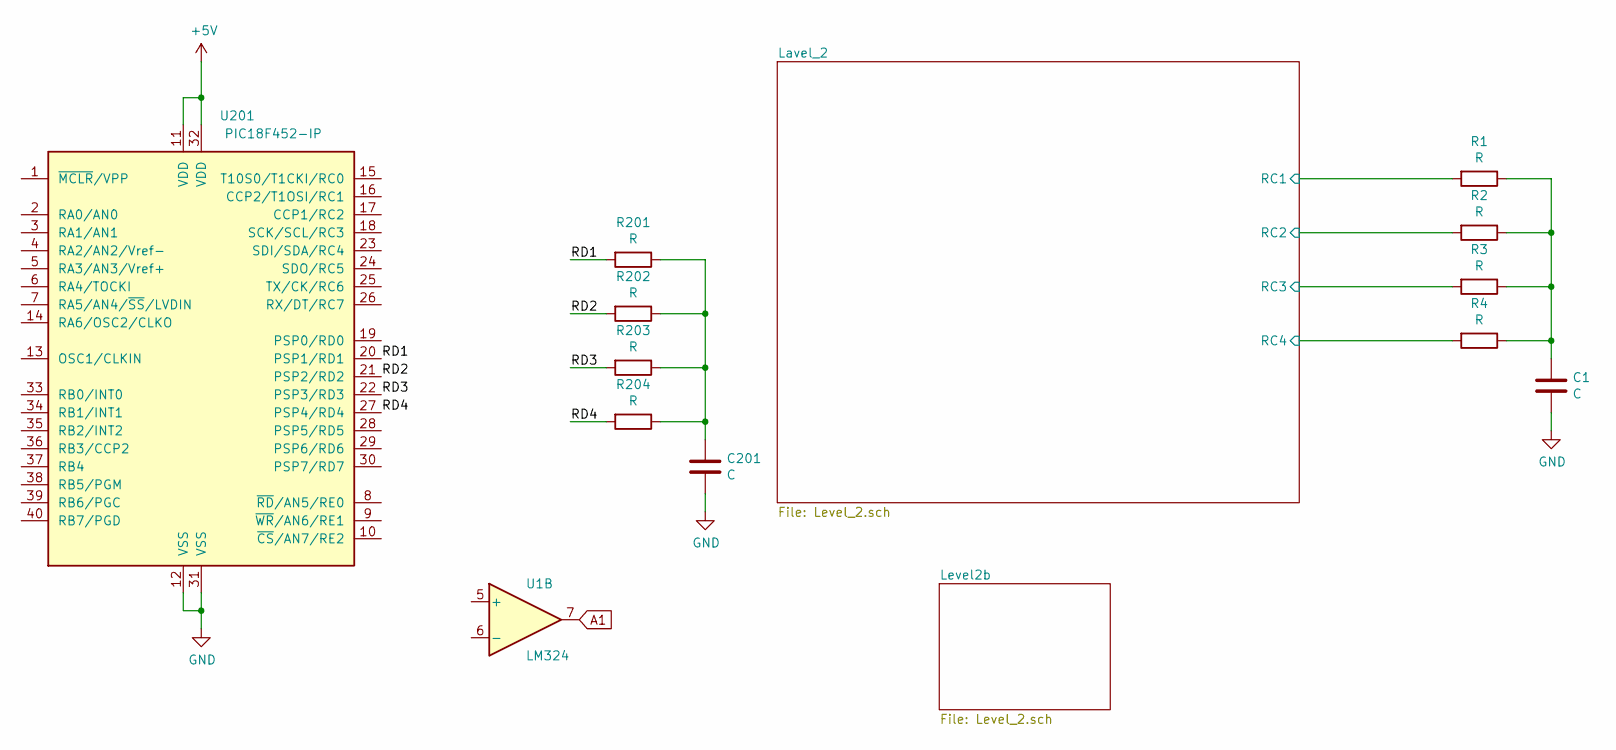
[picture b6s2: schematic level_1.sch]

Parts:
C1, C201: C; C_Disc_D7.5mm_W5.0mm_P5.00mm
R1, R2, R3, R4, R201, R202, R203, R204: R; R_Axial_DIN0614_L14.3mm_D5.7mm_P20.32mm_Horizontal
U1: LM324
U201: PIC18F452-IP; DIP-40_W15.24mm

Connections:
+5V: U201.11 (VDD), U201.32 (VDD); also elsewhere on the board
/level_1/Lavel_2/RC1: R1.2; also elsewhere on the board
/level_1/Lavel_2/RC2: R2.2; also elsewhere on the board
/level_1/Lavel_2/RC3: R3.2; also elsewhere on the board
/level_1/Lavel_2/RC4: R4.2; also elsewhere on the board
/level_1/RD1: R201.2, U201.20 (PSP1/RD1)
/level_1/RD2: R202.2, U201.21 (PSP2/RD2)
/level_1/RD3: R203.2, U201.22 (PSP3/RD3)
/level_1/RD4: R204.2, U201.27 (PSP4/RD4)
A1: U1.7; also elsewhere on the board
GND: C1.2, C201.2, U201.12 (VSS), U201.31 (VSS); also elsewhere on the board
unnamed: C1.1, R1.1, R2.1, R3.1, R4.1
unnamed: C201.1, R201.1, R202.1, R203.1, R204.1
